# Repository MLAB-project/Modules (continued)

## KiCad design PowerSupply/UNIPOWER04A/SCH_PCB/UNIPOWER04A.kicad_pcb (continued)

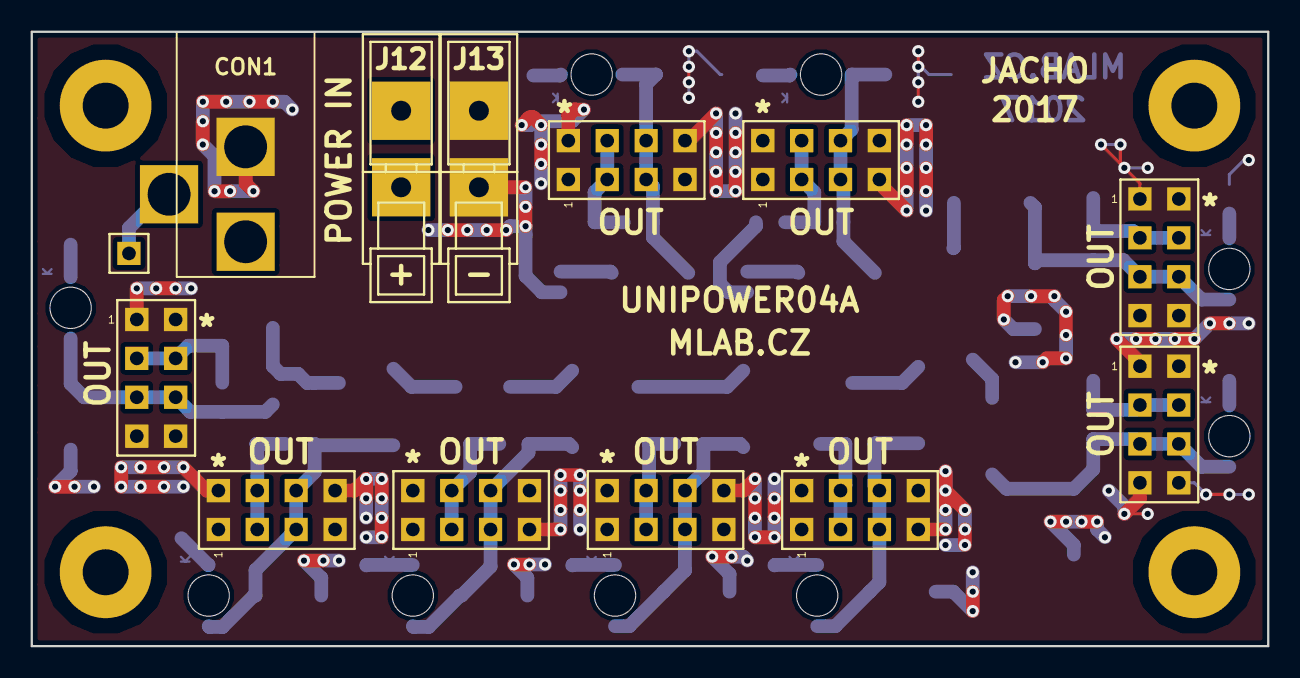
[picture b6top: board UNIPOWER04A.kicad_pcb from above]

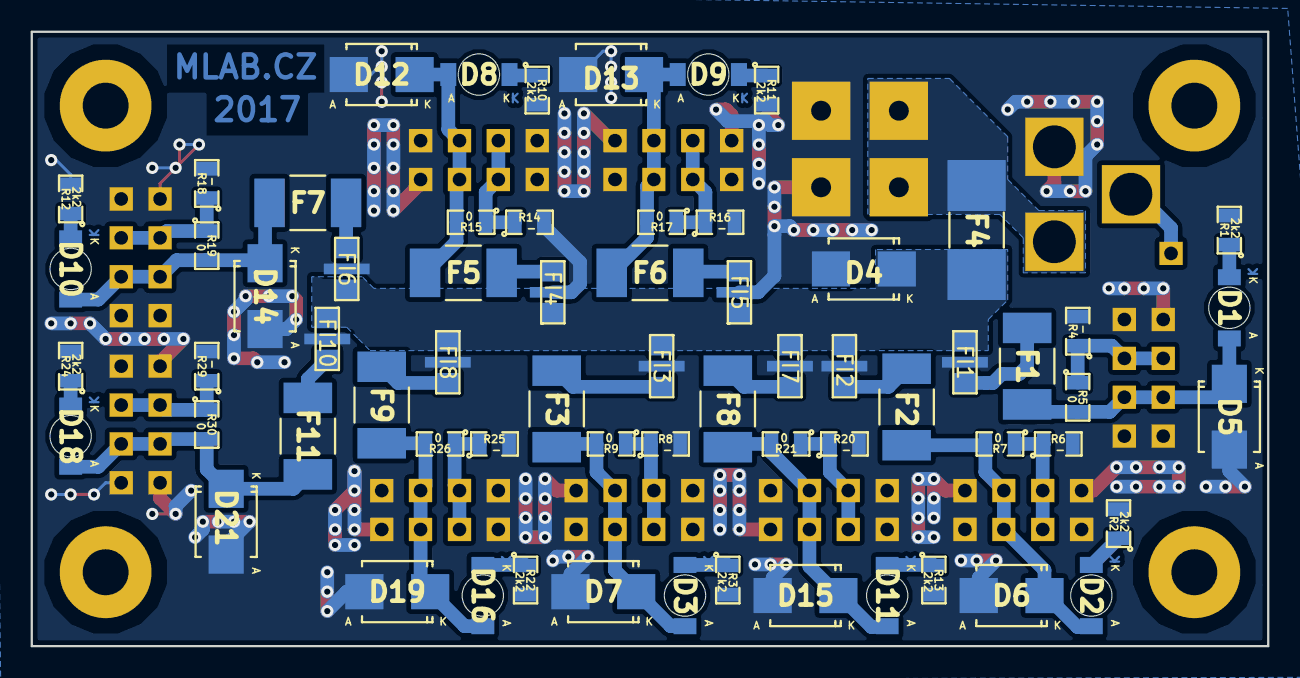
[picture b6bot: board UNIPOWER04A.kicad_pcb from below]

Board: 2 copper layers, 80.8 x 40.1 mm, 82 parts (65 on the bottom side), 40 nets.
